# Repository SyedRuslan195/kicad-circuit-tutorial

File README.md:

# kicad-circuit-tutorial
Basic circuit design and PCB layout for later manufacturing.
A serial in parallel out shifter is used with a clock signal as input resulting in leds turning on sequentially one after the other. The potentiometer allows to control the input clock frequency.

Schematic:

PCB layout:   

Final PCB:

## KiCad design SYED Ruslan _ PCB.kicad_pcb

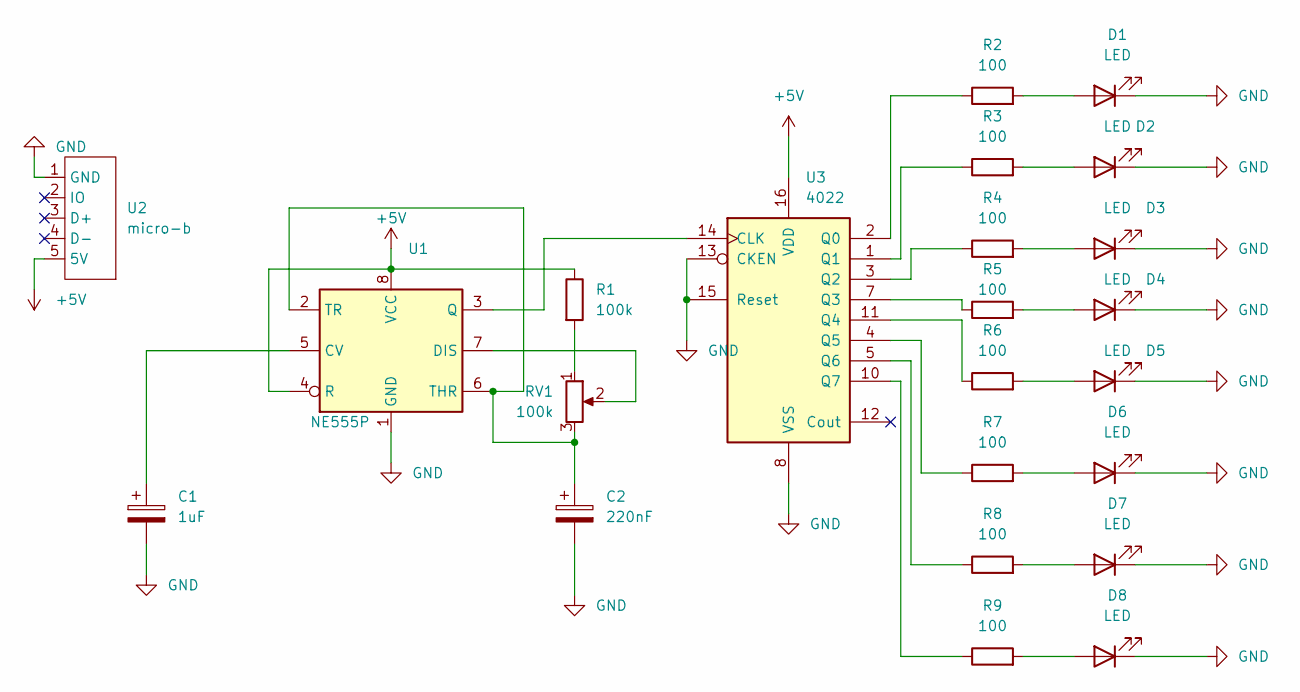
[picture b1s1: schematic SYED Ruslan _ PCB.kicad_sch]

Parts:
C1: 1uF; CP_Radial_D5.0mm_P2.00mm
C2: 220nF; CP_Radial_D5.0mm_P2.00mm
D1, D2, D3, D4, D5, D6, D7, D8: LED; LED_D5.0mm
R1: 100k; R_Axial_DIN0207_L6.3mm_D2.5mm_P10.16mm_Horizontal
R2, R3, R4, R5, R6, R7, R8, R9: 100; R_Axial_DIN0207_L6.3mm_D2.5mm_P10.16mm_Horizontal
RV1: 100k; Potentiometer_Bourns_PTV09A-1_Single_Vertical
U1: NE555P; DIP-8_W7.62mm
U2: micro-b; micro-b_adafruit
U3: 4022; DIP-16_W7.62mm

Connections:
+5V: R1.1, U1.4 (R), U1.8 (VCC), U2.5 (5V), U3.16 (VDD)
GND: C1.2, C2.2, D1.1 (K), D2.1 (K), D3.1 (K), D4.1 (K), D5.1 (K), D6.1 (K), D7.1 (K), D8.1 (K), U1.1 (GND), U2.1 (GND), U3.8 (VSS), U3.13 (CKEN), U3.15 (Reset)
unnamed: C1.1, U1.5 (CV)
unnamed: C2.1, RV1.3, U1.2 (TR), U1.6 (THR)
unnamed: D1.2 (A), R2.2
unnamed: D2.2 (A), R3.2
unnamed: D3.2 (A), R4.2
unnamed: D4.2 (A), R5.2
unnamed: D5.2 (A), R6.2
unnamed: D6.2 (A), R7.2
unnamed: D7.2 (A), R8.2
unnamed: D8.2 (A), R9.2
unnamed: R1.2, RV1.1
unnamed: R2.1, U3.2 (Q0)
unnamed: R3.1, U3.1 (Q1)
unnamed: R4.1, U3.3 (Q2)
unnamed: R5.1, U3.7 (Q3)
unnamed: R6.1, U3.11 (Q4)
unnamed: R7.1, U3.4 (Q5)
unnamed: R8.1, U3.5 (Q6)
unnamed: R9.1, U3.10 (Q7)
unnamed: RV1.2, U1.7 (DIS)
unnamed: U1.3 (Q), U3.14 (CLK)

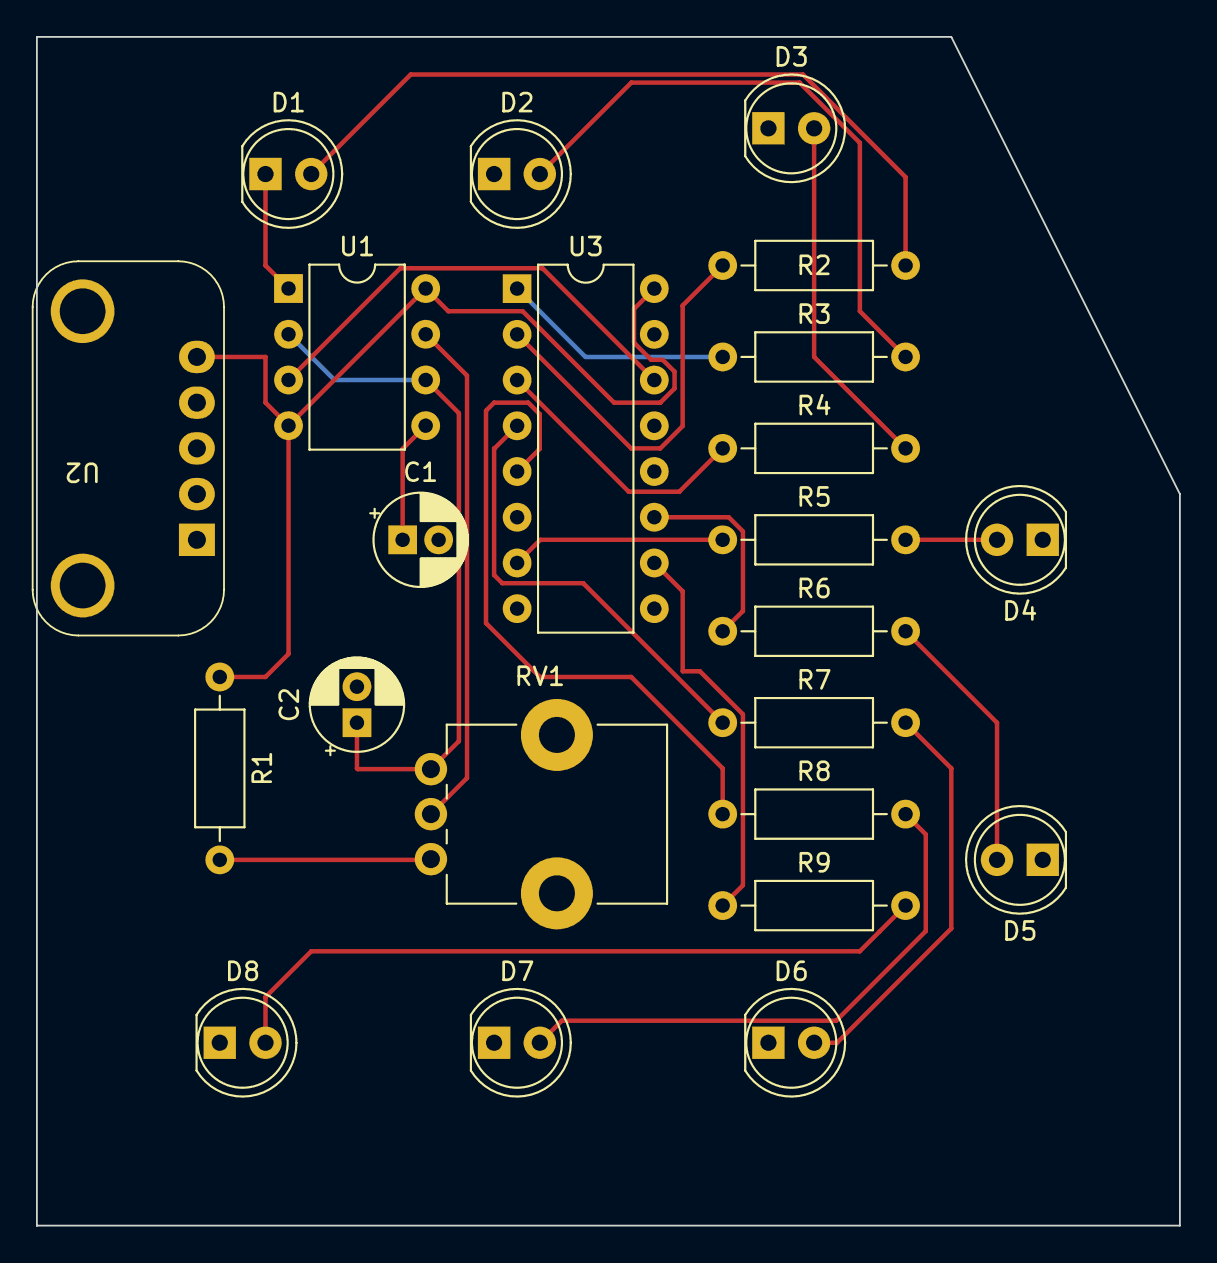
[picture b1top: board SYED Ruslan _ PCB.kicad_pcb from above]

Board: 2 copper layers, 63.5 x 66.0 mm, 23 parts (0 on the bottom side), 23 nets.
